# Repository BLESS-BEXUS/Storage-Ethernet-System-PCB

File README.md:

<p align="center">
    <br>
    
</p>
<h1 align="center">Storage & Ethernet System</h1>
<p align="center">
A compact PCB designed to provide redundant onboard storage and wired Ethernet connectivity for embedded systems where robustness, data integrity and easy integration are key.
</p>
<p align="center">

    <br>
    
</p>

---

### Overview

The main goal of this PCB is to improve the reliability of embedded data logging and communication systems.

It is especially useful in applications where removable media such as microSD cards may be affected by vibration, mechanical stress, poor contact or harsh environmental conditions.

The board is designed to support:

- Reliable onboard data storage.
- Redundant logging.
- Wired Ethernet communication.
- Compact integration.
- Post-operation data recovery.

### Main Features

- Dual SPI NOR Flash memories.
- Independent chip-select lines for each memory.
- WIZnet W5500 hardware TCP/IP Ethernet controller.
- SiTime SiT5000 25 MHz TCXO clock source.
- SPI interface with the main controller.
- ESD-aware external interface design.
- Ethernet analog supply isolation.
- Custom KiCad symbols, footprints and 3D models.

---

<h3 align="center">Contributing</h3>

<p align="center">
·
    <a href="./CODE_OF_CONDUCT.md">Code of Conduct</a>
    ·
    <a href="./CONTRIBUTING.md">Contributing Guide</a>
    ·
</p>

<p align="center">We welcome collaboration from the aerospace and software community. For major changes or data inquiries, please open an issue first.</p>

<h3 align="center">License</h3>

<pre align="center">Copyright © 2025-2026 The BLESS Project Team<br><br>This Source Code Form is subject to the terms of the Mozilla Public<br>License, v. 2.0. If a copy of the MPL was not distributed with this<br>file, You can obtain one at http://mozilla.org/MPL/2.0/.</pre>

<h3 align="center">Credits & Team</h3>

<p align="center">Supported by the REXUS/BEXUS Program and our generous sponsors.</p>
<p align="center">
    
</p>

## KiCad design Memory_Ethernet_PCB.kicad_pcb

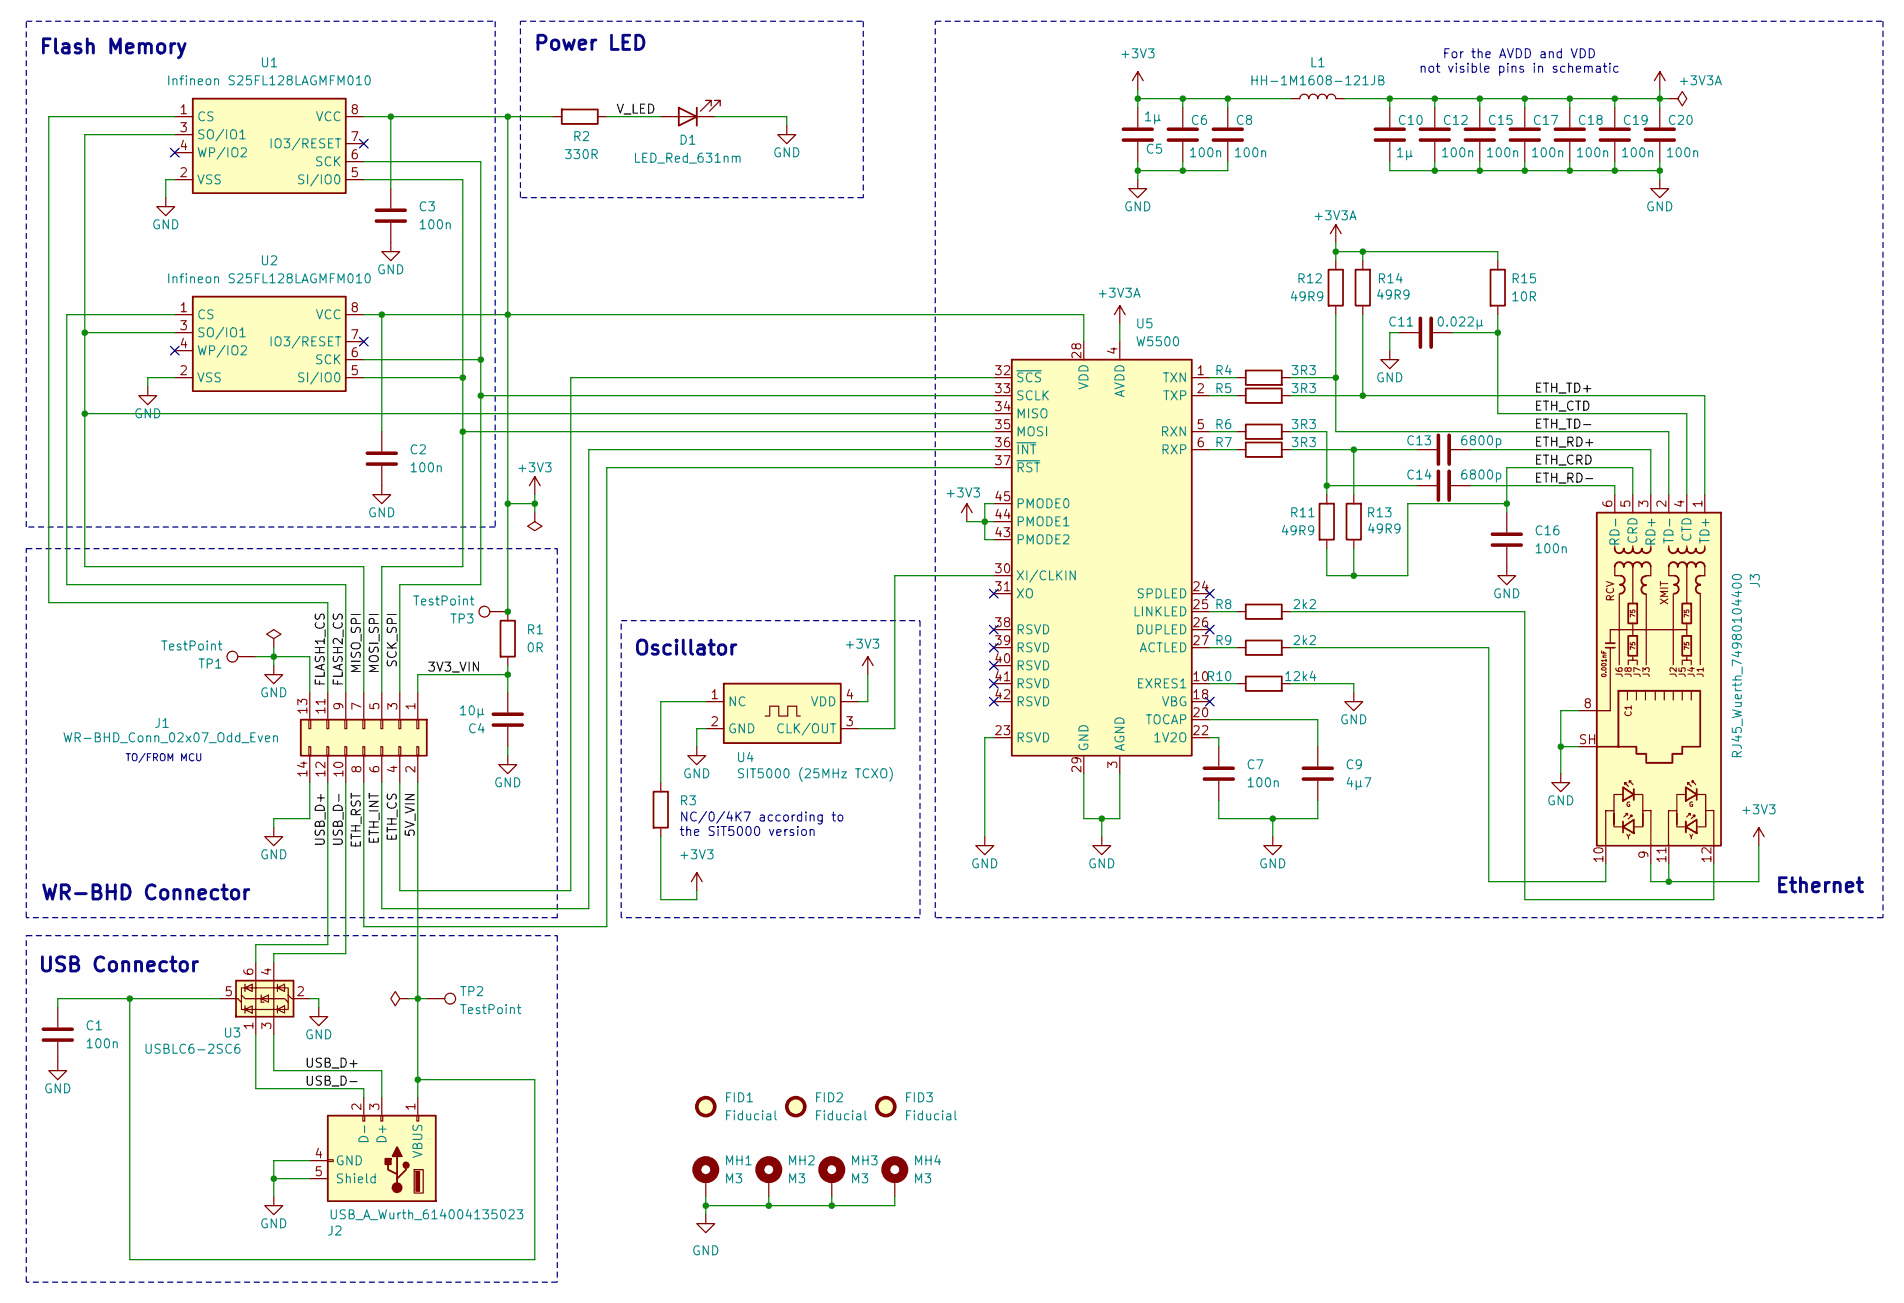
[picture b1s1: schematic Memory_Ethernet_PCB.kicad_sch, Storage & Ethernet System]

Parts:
C1, C2, C3, C6, C7, C8, C12, C15, C16, C17, C18, C19, C20: 100n; C_0805_2012Metric; Manufacturer Part Number GCD21BR71H104KA01K; LCSC C21025875
C4: 10µ; C_1206_3216Metric; Manufacturer Part Number CGA5L1X7R1C106K160AC; LCSC C2168241
C5, C10: 1µ; C_0805_2012Metric; Manufacturer Part Number KGM21AR71C105JU; LCSC C20219896
C9: 4µ7; C_0805_2012Metric; Manufacturer Part Number GCM21BM8EH475KE08L
C11: 0.022µ; C_0805_2012Metric; Manufacturer Part Number GCM21B5C2A223JE02L; LCSC C21025875
C13, C14: 6800p; C_0805_2012Metric; Manufacturer Part Number GRM21AR7LU682KW01D
D1: LED_Red_631nm; LED_0603_1608Metric; Manufacturer Part Number LTST-C190KRKT; LCSC C94869
FID1, FID2, FID3: Fiducial; Fiducial_1mm_Mask2mm
J1: WR-BHD_Conn_02x07_Odd_Even; IDC-Header_2x07_P2.54mm_Vertical
J2: USB_A_Wurth_614004135023
J3: RJ45_Wuerth_74980104400
L1: HH-1M1608-121JB; L_0603_1608Metric
MH1, MH2, MH3, MH4: M3; MountingHole_3.2mm_M3_Pad_Via
R1: 0R; R_0603_1608Metric; Manufacturer Part Number RC0603JR-070RL; LCSC C95177
R2: 330R; R_0603_1608Metric; Manufacturer Part Number CR0603-FX-3300ELF; LCSC C2077087
R3: R_0805_2012Metric; Manufacturer Part Number AC0805JR-134K7L; LCSC C6457914
R4, R5, R6, R7: 3R3; R_0805_2012Metric; Manufacturer Part Number RC0805FR-073R3P; LCSC C20162778
R8, R9: 2k2; R_0805_2012Metric; Manufacturer Part Number AC0805FR-7W2K2L; LCSC C5545398
R10: 12k4; R_0805_2012Metric; Manufacturer Part Number ERJ-UP6F1242V; LCSC C7184516
R11, R12, R13, R14: 49R9; R_0805_2012Metric; Manufacturer Part Number RT73F2A49R9BTD; LCSC C95177
R15: 10R; R_0805_2012Metric; Manufacturer Part Number CRGP0805F10R; LCSC C2083624
TP1, TP2, TP3: TestPoint; TestPoint_Pad_D1.0mm
U1, U2: Infineon S25FL128LAGMFM010; SOIC-8_5.3x5.3mm_P1.27mm; LCSC C2944449
U3: USBLC6-2SC6; SOT-23-6; LCSC C7519
U4: SIT5000 (25MHz TCXO); Oscillator_SMD_SiT_PQFN-4Pin_2.5x2.0mm
U5: W5500; LQFP-48_7x7mm_P0.5mm

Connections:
+3V3: C2.1, C3.1, C5.2, C6.1, C8.1, J3.9, J3.11, L1.1, R1.1, R2.2, R3.2, TP3.1 (1_1), U1.8 (VCC), U2.8 (VCC), U4.4 (VDD), U5.28 (VDD), U5.43 (PMODE2), U5.44 (PMODE1), U5.45 (PMODE0)
+3V3A: C10.1, C12.1, C15.1, C17.1, C18.1, C19.1, C20.1, L1.2, R12.1, R14.2, R15.1, U5.4 (AVDD), U5.8 (AVDD), U5.11 (AVDD), U5.15 (AVDD), U5.17 (AVDD), U5.21 (AVDD)
/3V3_VIN: C4.1, J1.1, R1.2
/5V_VIN: C1.1, J1.2, J2.1 (VBUS), TP2.1 (1_1), U3.5 (VBUS)
/ETH_CRD: C16.1, J3.5 (CRD), R11.2, R13.1
/ETH_CS: J1.4, U5.32 (~SCS)
/ETH_CTD: C11.2, J3.4 (CTD), R15.2
/ETH_INT: J1.6, U5.36 (~INT)
/ETH_RD+: C13.2, J3.3 (RD+)
/ETH_RD-: C14.2, J3.6 (RD-)
/ETH_RST: J1.8, U5.37 (~RST)
/ETH_TD+: J3.1 (TD+), R5.2, R14.1
/ETH_TD-: J3.2 (TD-), R4.2, R12.2
/FLASH1_CS: J1.11, U1.1 (CS)
/FLASH2_CS: J1.9, U2.1 (CS)
/MISO_SPI: J1.7, U1.3 (SO/IO1), U2.3 (SO/IO1), U5.34 (MISO)
/MOSI_SPI: J1.5, U1.5 (SI/IO0), U2.5 (SI/IO0), U5.35 (MOSI)
/SCK_SPI: J1.3, U1.6 (SCK), U2.6 (SCK), U5.33 (SCLK)
/USB_D+: J1.12, J2.3 (D+), U3.3 (I/O2), U3.6 (I/O1)
/USB_D-: J1.10, J2.2 (D-), U3.1 (I/O1), U3.4 (I/O2)
/V_LED: D1.2 (A), R2.1
GND: C1.2, C2.2, C3.2, C4.2, C5.1, C6.2, C7.2, C8.2, C9.2, C10.2, C11.1, C12.2, C15.2, C16.2, C17.2, C18.2, C19.2, C20.2, D1.1 (K), J1.13, J1.14, J2.4 (GND), J2.5 (Shield), J3.8, J3.SH, MH1.1 (1_1), MH2.1 (1_1), MH3.1 (1_1), MH4.1 (1_1), R10.2, TP1.1 (1_1), U1.2 (VSS), U2.2 (VSS), U3.2 (GND), U4.2 (GND), U5.3 (AGND), U5.9 (AGND), U5.14 (AGND), U5.16 (AGND), U5.19 (AGND), U5.23 (RSVD), U5.29 (GND), U5.48 (AGND)
unnamed: C13.1, R7.2, R13.2
unnamed: C14.1, R6.2, R11.1
unnamed: J3.10, R9.2
unnamed: J3.12, R8.2
unnamed: U4.3 (CLK/OUT), U5.30 (XI/CLKIN)
unnamed: R3.1, U4.1 (NC)
unnamed: C7.1, U5.22 (1V2O)
unnamed: R9.1, U5.27 (ACTLED)
unnamed: R10.1, U5.10 (EXRES1)
unnamed: R8.1, U5.25 (LINKLED)
unnamed: R6.1, U5.5 (RXN)
unnamed: R7.1, U5.6 (RXP)
unnamed: C9.1, U5.20 (TOCAP)
unnamed: R4.1, U5.1 (TXN)
unnamed: R5.1, U5.2 (TXP)

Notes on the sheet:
TO/FROM MCU
Power LED
Flash Memory
Ethernet
NC/0/4K7 according to the SiT5000 version
USB Connector
For the AVDD and VDD not visible pins in schematic
WR-BHD Connector
Oscillator

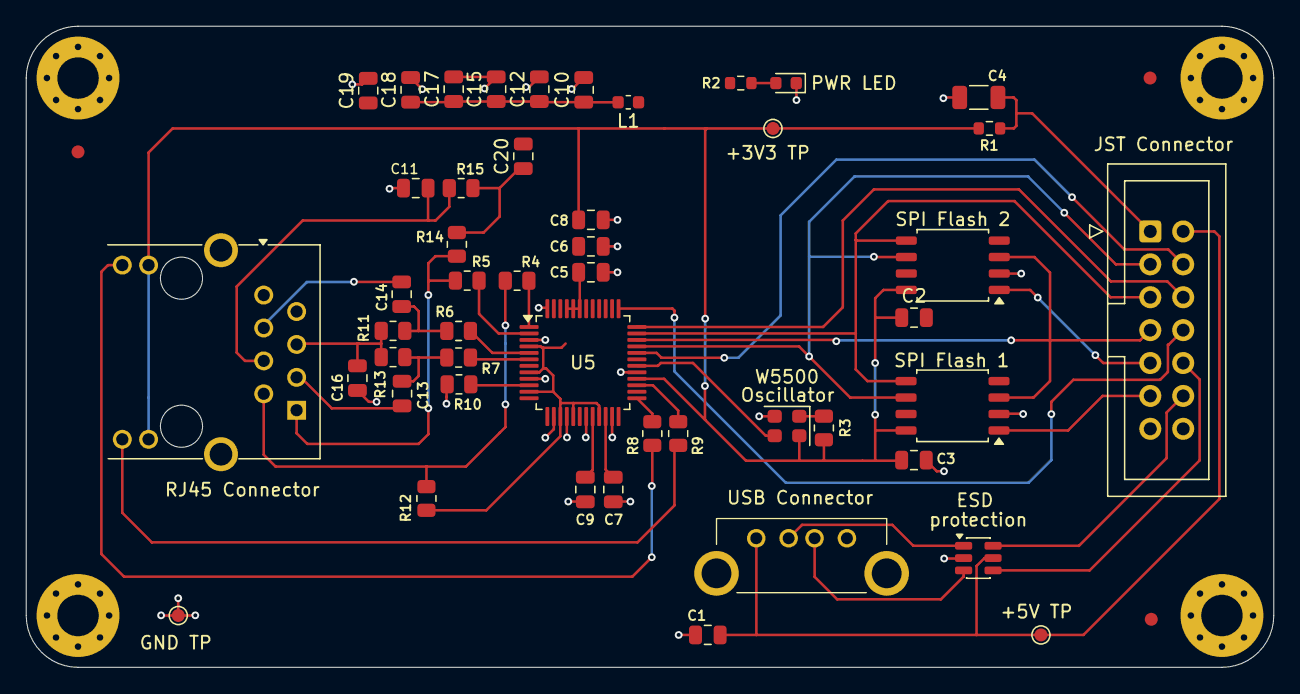
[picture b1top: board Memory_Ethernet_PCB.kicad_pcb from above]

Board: 2 copper layers, 96.3 x 49.5 mm, 55 parts (0 on the bottom side), 37 nets.

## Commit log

2026-06-12 Add .gitignore file for KiCad project to exclude temporary and backup files
2026-06-12 Add .DS_Store to .gitignore to exclude MacOS metadata files
2026-06-12 git commit -m "Add initial Memory Ethernet PCB KiCad project
    Include the main KiCad project files for the Memory Ethernet PCB:
    schematic, PCB layout, and project configuration. This commit establishes
    the base hardware design to track future changes in version control."
2026-06-12 Add custom STEP models for non-standard components
    Include 3D STEP models required by components that are not available
    in the default KiCad libraries, ensuring the PCB 3D view and mechanical
    integration remain consistent across the project.
2026-06-12 Add project-specific KiCad symbol and footprint libraries
    Add the custom schematic symbol library, footprint library, and KiCad
    library tables required to make the PCB project portable and consistent
    across different development environments.
2026-06-12 Add project README
2026-06-12 Remove pcb routing
2026-06-12 Remove extra header
2026-06-14 Initial component routing
2026-06-14 SPI and ETH Routing
2026-06-14 +3V3 Routing
